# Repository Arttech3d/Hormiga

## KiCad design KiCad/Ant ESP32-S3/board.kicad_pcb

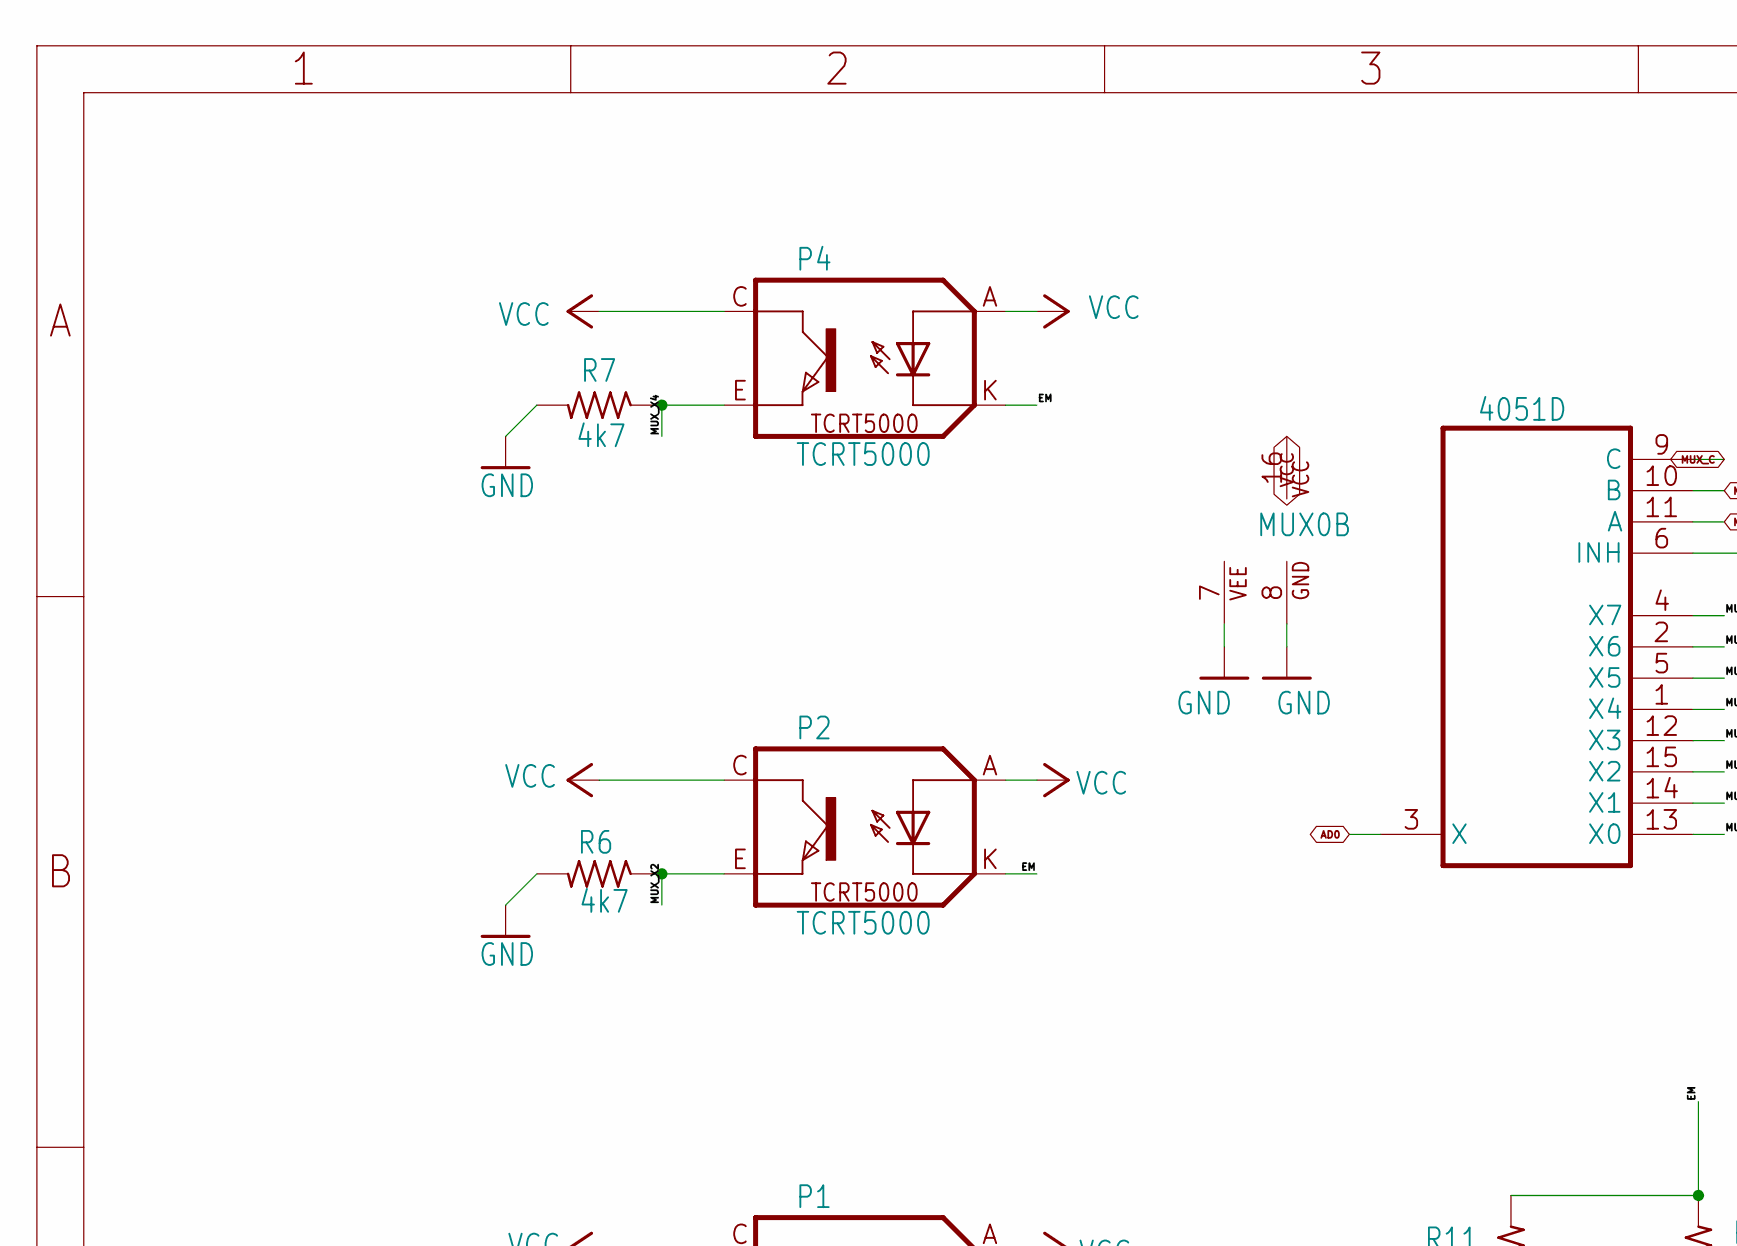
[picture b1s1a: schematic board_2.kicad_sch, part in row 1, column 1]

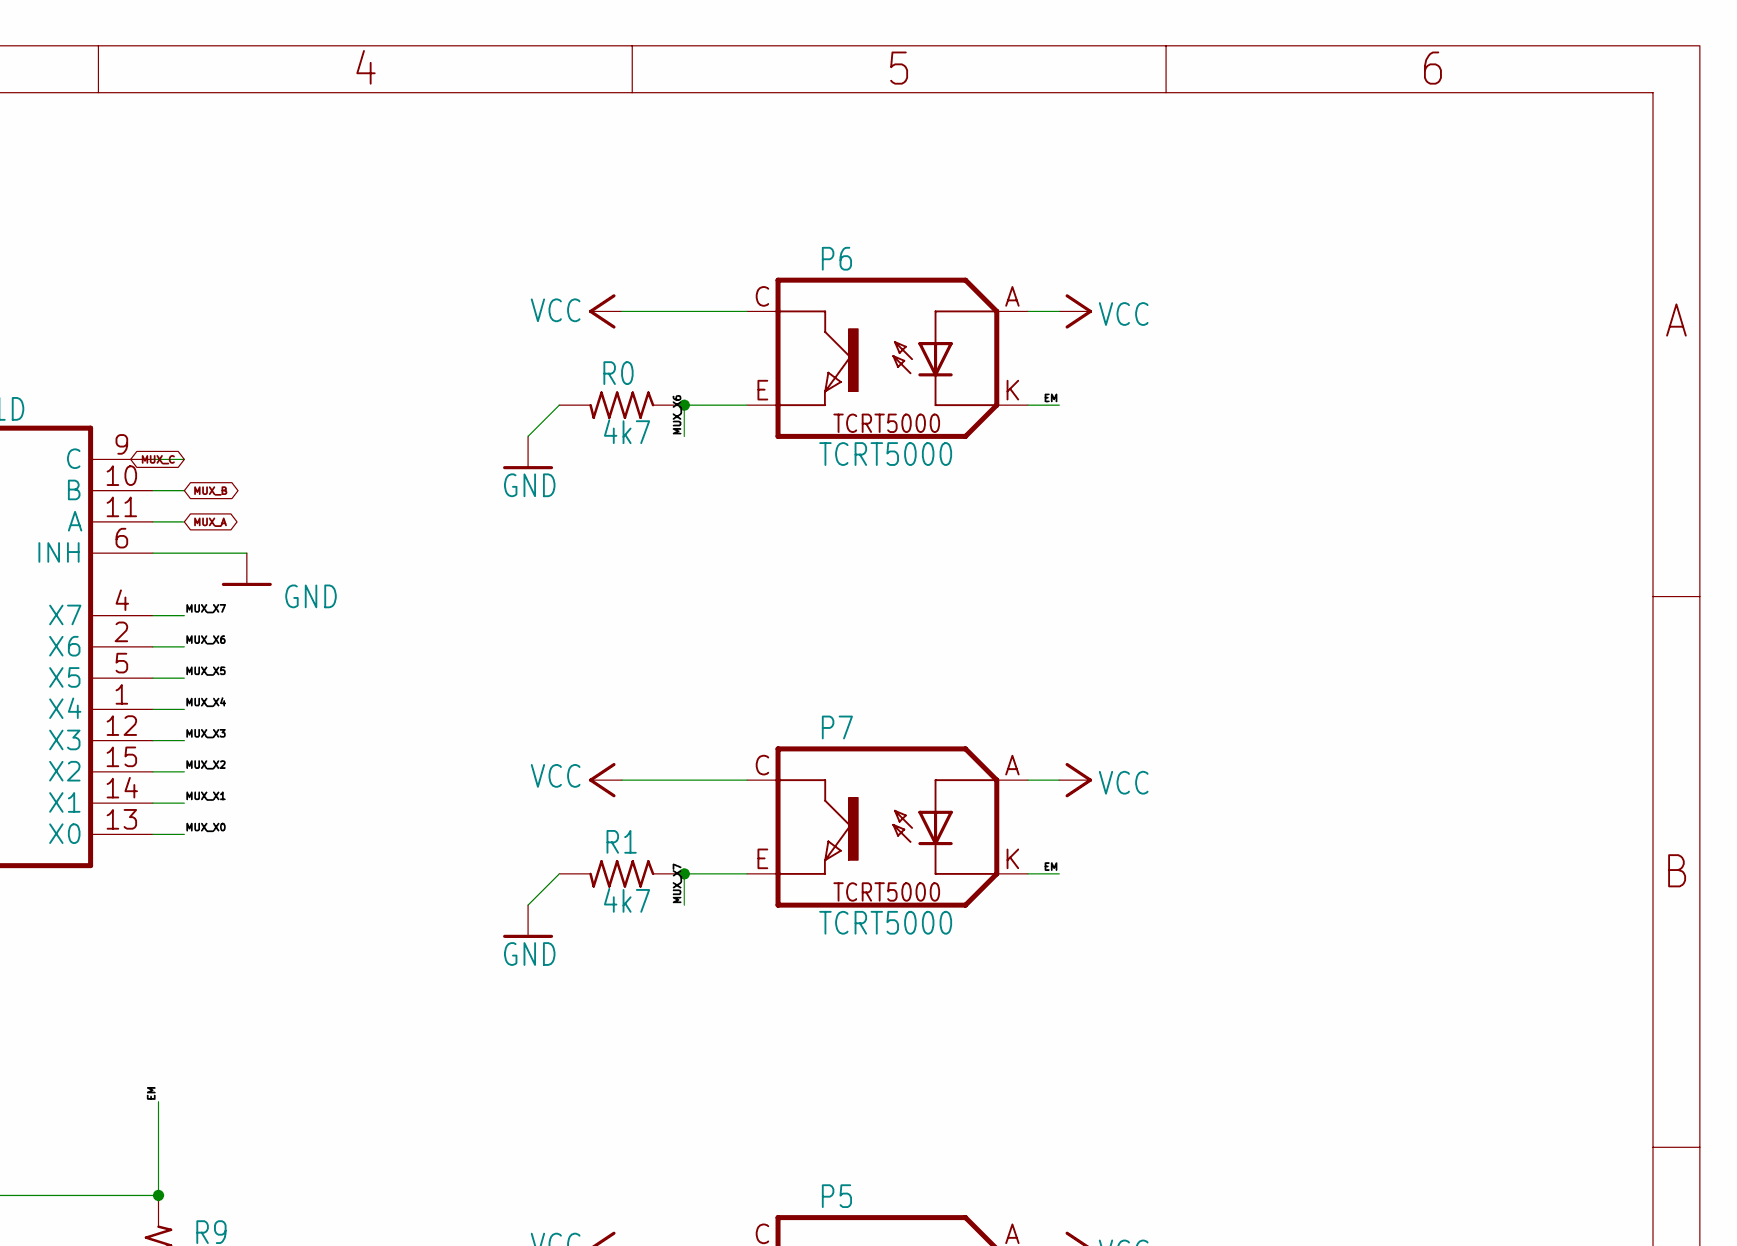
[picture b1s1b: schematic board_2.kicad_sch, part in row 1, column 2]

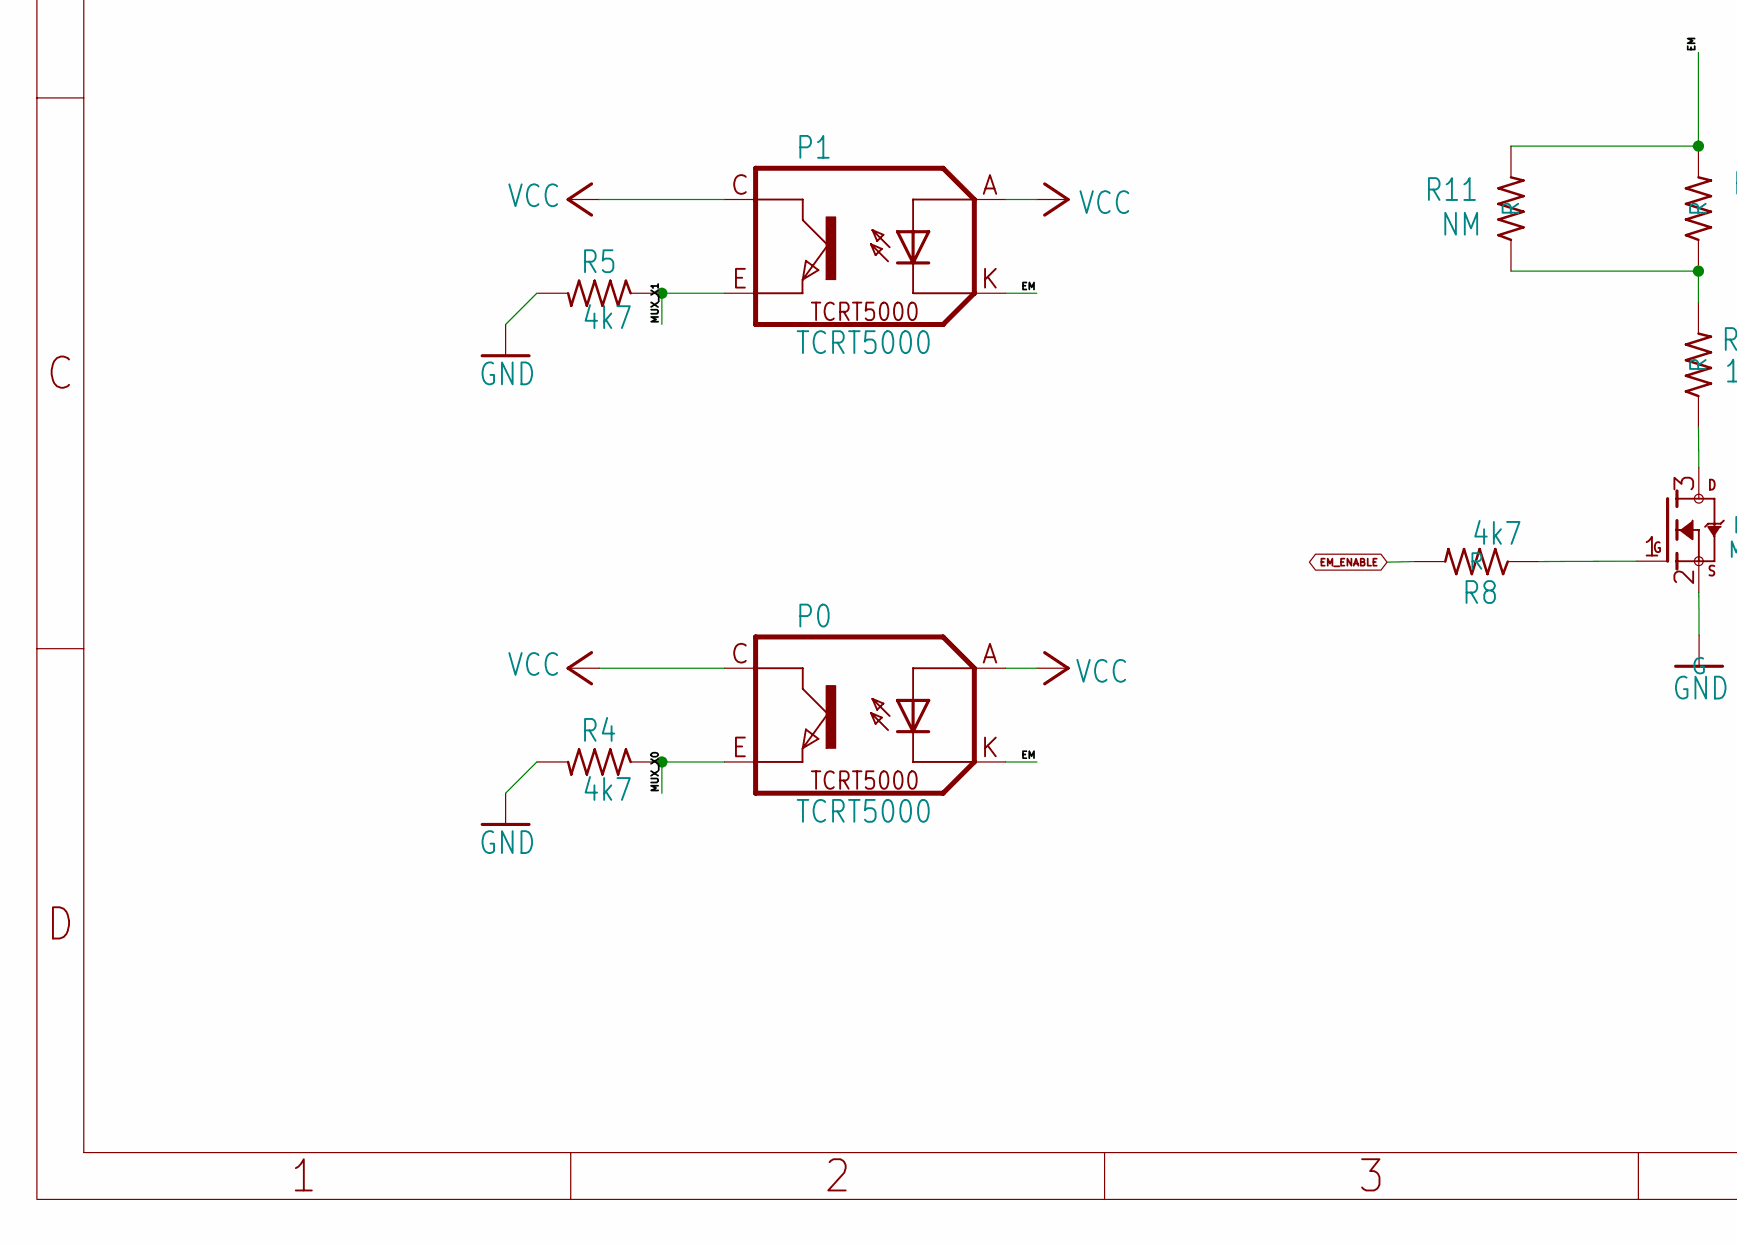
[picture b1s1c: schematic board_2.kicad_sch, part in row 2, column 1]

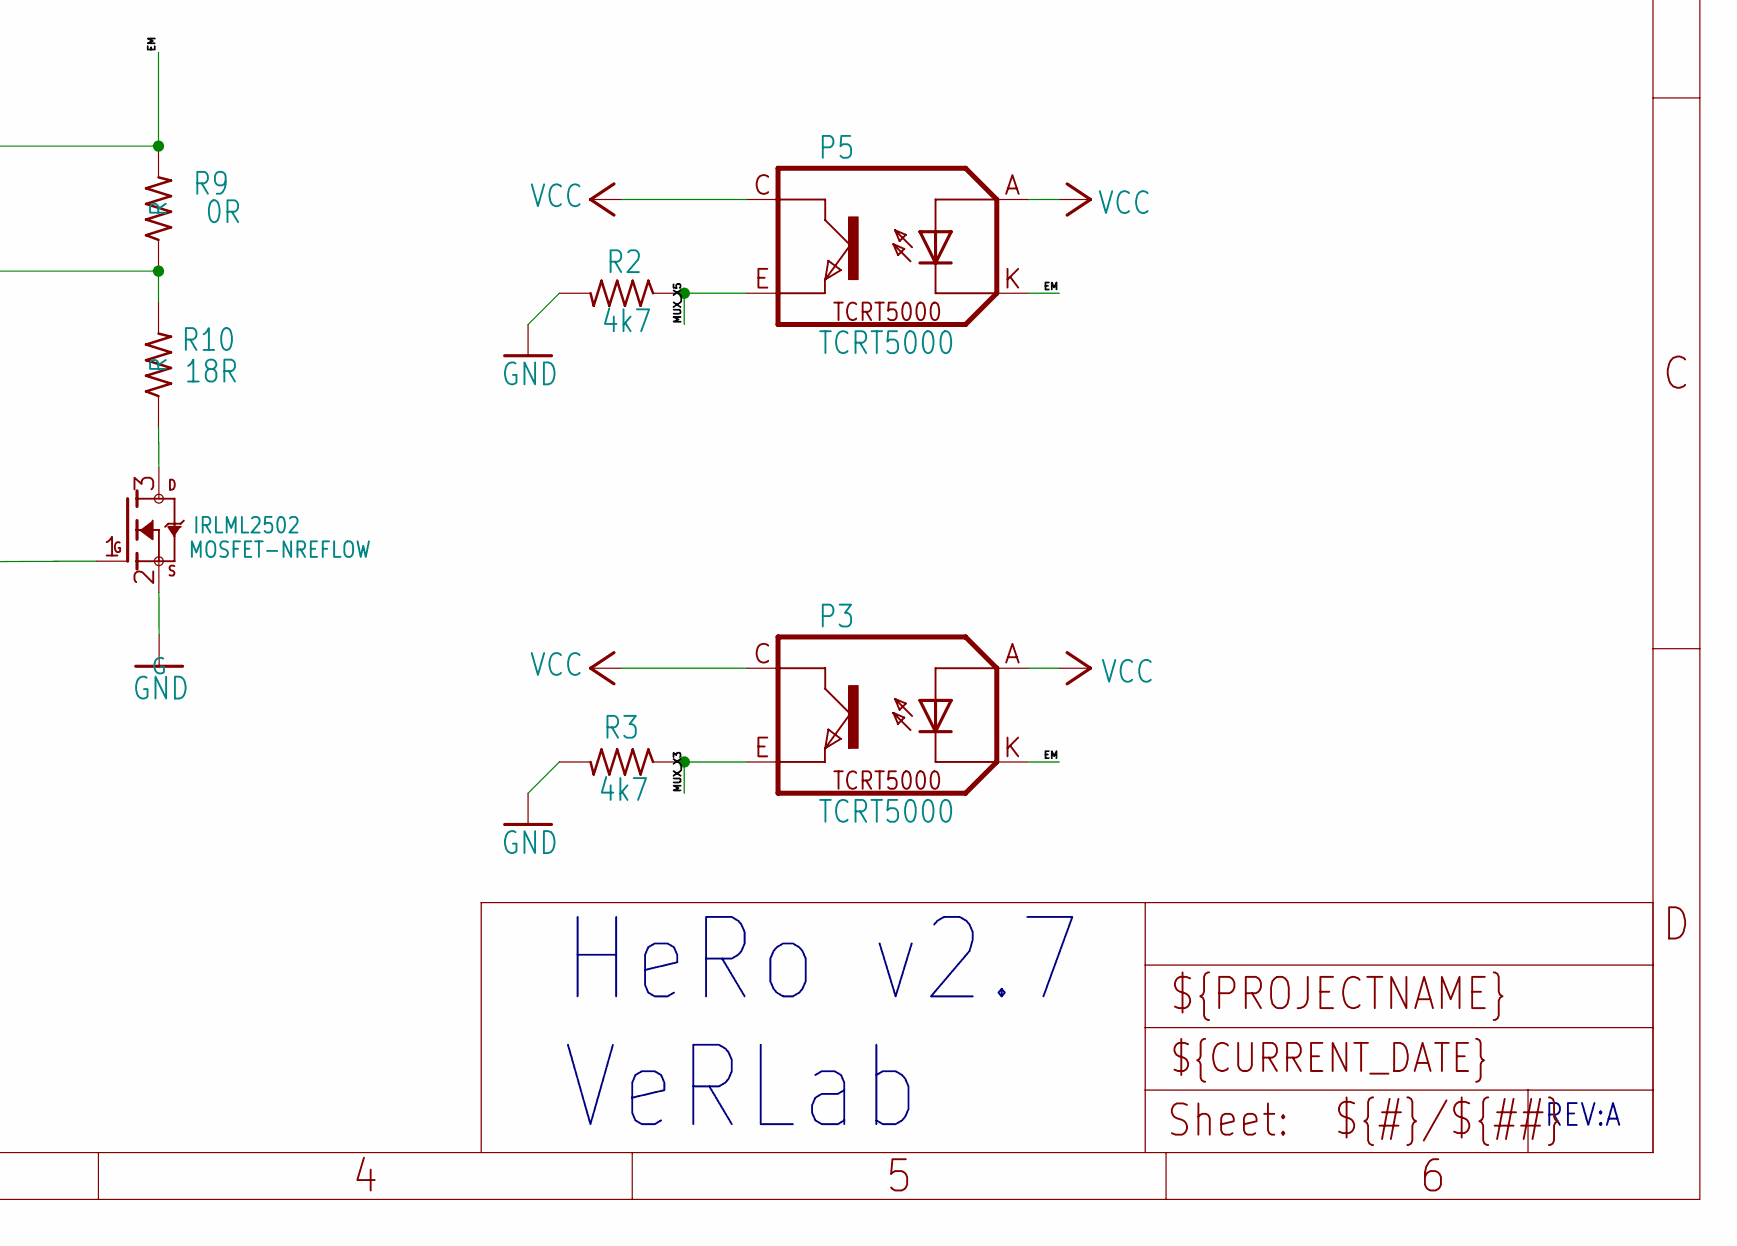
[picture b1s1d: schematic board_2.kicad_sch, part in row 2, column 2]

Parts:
IRLML2502: MOSFET-NREFLOW; SOT23
MUX0: 4051D; SO16
P0, P1, P2, P3, P4, P5, P6, P7: TCRT5000
R0, R1, R2, R3, R4, R5, R6, R7: 4k7; M0805
R8: 4k7; R0805
R9: 0R; R0805
R10: 18R; R0805
R11: NM; R0805

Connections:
/<p>Proximity Sensors</p>/EM: P0.K (CATHODE), P1.K (CATHODE), P2.K (CATHODE), P3.K (CATHODE), P4.K (CATHODE), P5.K (CATHODE), P6.K (CATHODE), P7.K (CATHODE), R9.2, R11.2
/<p>Proximity Sensors</p>/MUX_X0: MUX0.13 (X0), P0.E (EMITTER), R4.1
/<p>Proximity Sensors</p>/MUX_X1: MUX0.14 (X1), P1.E (EMITTER), R5.1
/<p>Proximity Sensors</p>/MUX_X2: MUX0.15 (X2), P2.E (EMITTER), R6.1
/<p>Proximity Sensors</p>/MUX_X3: MUX0.12 (X3), P3.E (EMITTER), R3.1
/<p>Proximity Sensors</p>/MUX_X4: MUX0.1 (X4), P4.E (EMITTER), R7.1
/<p>Proximity Sensors</p>/MUX_X5: MUX0.5 (X5), P5.E (EMITTER), R2.1
/<p>Proximity Sensors</p>/MUX_X6: MUX0.2 (X6), P6.E (EMITTER), R0.1
/<p>Proximity Sensors</p>/MUX_X7: MUX0.4 (X7), P7.E (EMITTER), R1.1
AD0: MUX0.3 (X); also elsewhere on the board
EM_ENABLE: R8.2; also elsewhere on the board
GND: IRLML2502.2 (S), MUX0.6 (INH), MUX0.7 (VEE), MUX0.8 (GND), R0.2, R1.2, R2.2, R3.2, R4.2, R5.2, R6.2, R7.2; also elsewhere on the board
MUX_A: MUX0.11 (A); also elsewhere on the board
MUX_B: MUX0.10 (B); also elsewhere on the board
MUX_C: MUX0.9 (C); also elsewhere on the board
unnamed: IRLML2502.3 (D), R10.1
unnamed: IRLML2502.1 (G), R8.1
unnamed: R9.1, R10.2, R11.1
VCC: MUX0.16 (VCC), P0.A (ANODE), P0.C (COLLECTOR), P1.A (ANODE), P1.C (COLLECTOR), P2.A (ANODE), P2.C (COLLECTOR), P3.A (ANODE), P3.C (COLLECTOR), P4.A (ANODE), P4.C (COLLECTOR), P5.A (ANODE), P5.C (COLLECTOR), P6.A (ANODE), P6.C (COLLECTOR), P7.A (ANODE), P7.C (COLLECTOR); also elsewhere on the board

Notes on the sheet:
HeRo v2.7 VeRLab
REV:A

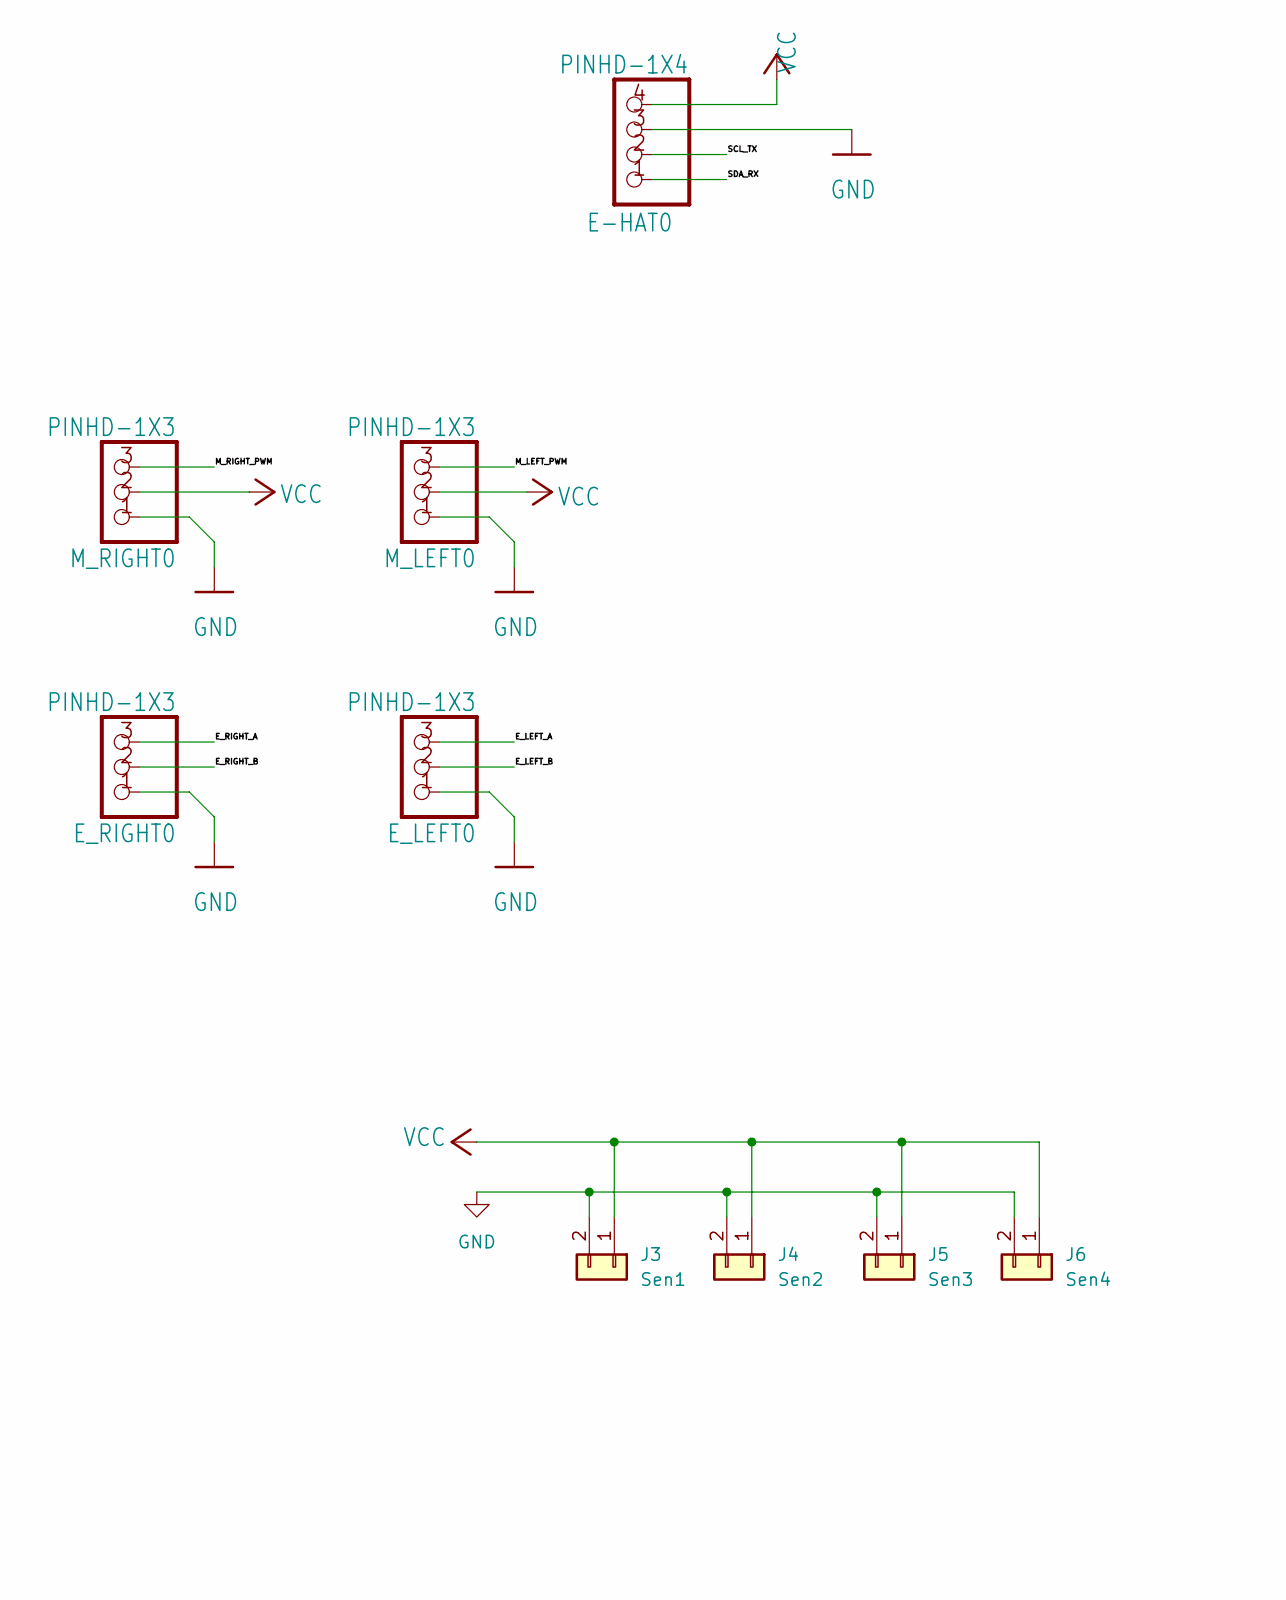
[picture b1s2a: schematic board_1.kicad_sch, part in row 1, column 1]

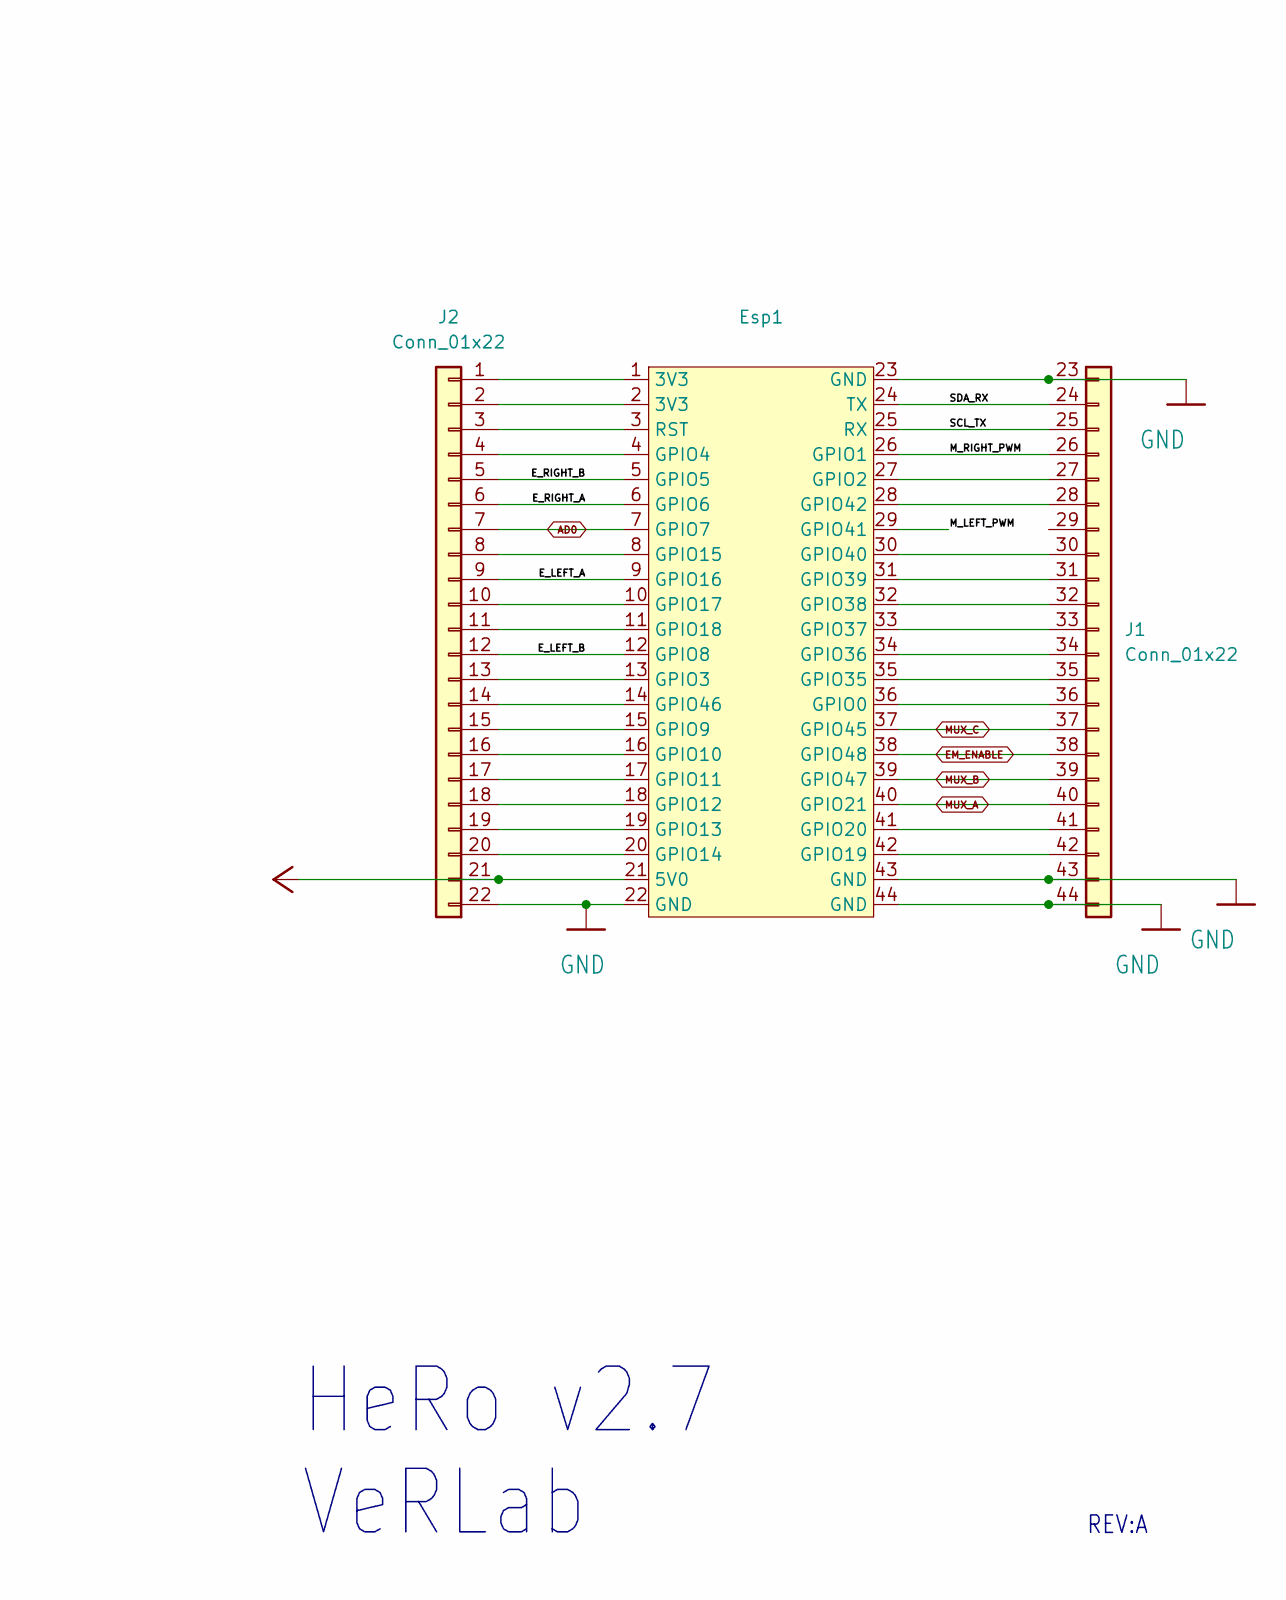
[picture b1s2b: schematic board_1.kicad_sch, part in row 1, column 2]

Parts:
E-HAT0: PINHD-1X4; 1X04
E_LEFT0: PINHD-1X3; 1X03
E_RIGHT0: PINHD-1X3; 1X03
Esp1: Untitled
J1, J2: Conn_01x22; PinHeader_1x22_P2.54mm_Vertical
J3: Sen1; PinHeader_1x02_P2.00mm_Vertical
J4: Sen2; PinHeader_1x02_P2.00mm_Vertical
J5: Sen3; PinHeader_1x02_P2.00mm_Vertical
J6: Sen4; PinHeader_1x02_P2.00mm_Vertical
M_LEFT0: PINHD-1X3; 1X03
M_RIGHT0: PINHD-1X3; 1X03

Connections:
/<p>MCU and Motors</p>/E_LEFT_A: E_LEFT0.3, Esp1.9 (GPIO16), J2.9 (Pin_14)
/<p>MCU and Motors</p>/E_LEFT_B: E_LEFT0.2, Esp1.12 (GPIO8), J2.12 (Pin_11)
/<p>MCU and Motors</p>/E_RIGHT_A: E_RIGHT0.3, Esp1.6 (GPIO6), J2.6 (Pin_17)
/<p>MCU and Motors</p>/E_RIGHT_B: E_RIGHT0.2, Esp1.5 (GPIO5), J2.5 (Pin_18)
/<p>MCU and Motors</p>/M_LEFT_PWM: Esp1.29 (GPIO41), M_LEFT0.3
/<p>MCU and Motors</p>/M_RIGHT_PWM: Esp1.26 (GPIO1), J1.26 (Pin_4), M_RIGHT0.3
/<p>MCU and Motors</p>/SCL_TX: E-HAT0.2, Esp1.25 (RX), J1.25 (Pin_3)
/<p>MCU and Motors</p>/SDA_RX: E-HAT0.1, Esp1.24 (TX), J1.24
AD0: Esp1.7 (GPIO7), J2.7 (Pin_16); also elsewhere on the board
EM_ENABLE: Esp1.38 (GPIO48), J1.38 (Pin_16); also elsewhere on the board
GND: E-HAT0.3, E_LEFT0.1, E_RIGHT0.1, Esp1.22 (GND), Esp1.23 (GND), Esp1.43 (GND), Esp1.44 (GND), J1.23, J1.43 (Pin_21), J1.44 (Pin_22), J2.22 (Pin_1), J3.2, J4.2, J5.2, J6.2, M_LEFT0.1, M_RIGHT0.1; also elsewhere on the board
MUX_A: Esp1.40 (GPIO21), J1.40 (Pin_18); also elsewhere on the board
MUX_B: Esp1.39 (GPIO47), J1.39 (Pin_17); also elsewhere on the board
MUX_C: Esp1.37 (GPIO45), J1.37 (Pin_15); also elsewhere on the board
unnamed: Esp1.1 (3V3), J2.1
unnamed: Esp1.36 (GPIO0), J1.36 (Pin_14)
unnamed: Esp1.27 (GPIO2), J1.27 (Pin_5)
unnamed: Esp1.13 (GPIO3), J2.13 (Pin_10)
unnamed: Esp1.4 (GPIO4), J2.4 (Pin_19)
unnamed: Esp1.15 (GPIO9), J2.15 (Pin_8)
unnamed: Esp1.16 (GPIO10), J2.16 (Pin_7)
unnamed: Esp1.17 (GPIO11), J2.17 (Pin_6)
unnamed: Esp1.18 (GPIO12), J2.18 (Pin_5)
unnamed: Esp1.19 (GPIO13), J2.19 (Pin_4)
unnamed: Esp1.20 (GPIO14), J2.20 (Pin_3)
unnamed: Esp1.8 (GPIO15), J2.8 (Pin_15)
unnamed: Esp1.10 (GPIO17), J2.10 (Pin_13)
unnamed: Esp1.11 (GPIO18), J2.11 (Pin_12)
unnamed: Esp1.42 (GPIO19), J1.42 (Pin_20)
unnamed: Esp1.41 (GPIO20), J1.41 (Pin_19)
unnamed: Esp1.35 (GPIO35), J1.35 (Pin_13)
unnamed: Esp1.34 (GPIO36), J1.34 (Pin_12)
unnamed: Esp1.33 (GPIO37), J1.33 (Pin_11)
unnamed: Esp1.32 (GPIO38), J1.32 (Pin_10)
unnamed: Esp1.31 (GPIO39), J1.31 (Pin_9)
unnamed: Esp1.30 (GPIO40), J1.30 (Pin_8)
unnamed: Esp1.28 (GPIO42), J1.28 (Pin_6)
unnamed: Esp1.14 (GPIO46), J2.14 (Pin_9)
unnamed: Esp1.3 (RST), J2.3 (Pin_20)
unnamed: Esp1.2 (3V3), J2.2 (Pin_21)
VCC: E-HAT0.4, Esp1.21 (5V0), J2.21 (Pin_2), J3.1, J4.1, J5.1, J6.1, M_LEFT0.2, M_RIGHT0.2; also elsewhere on the board

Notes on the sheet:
HeRo v2.7 VeRLab
REV:A

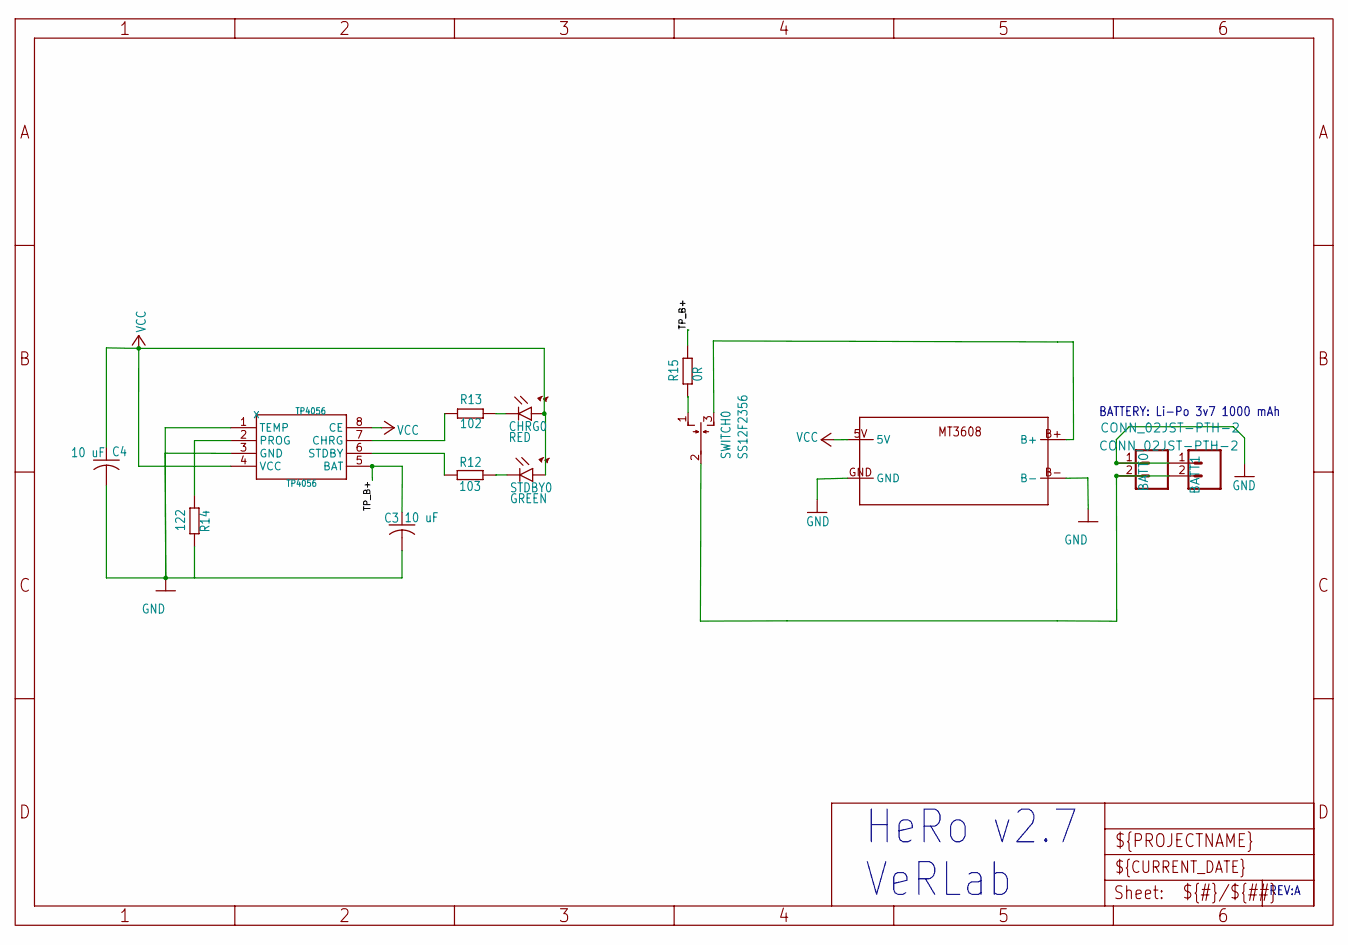
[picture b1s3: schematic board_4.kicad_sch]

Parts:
BATT0, BATT1: CONN_02JST-PTH-2; JST-2-PTH
C3, C4: 10 uF; C0603_420
CHRG0: RED; SML0805
MT3608: MT3608
R12: 103; R0805
R13: 102; R0805
R14: 122; R0603
R15: 0R; R0805
STDBY0: GREEN; SML0805
SWITCH0: SS12F2356; HH3T90
TP4056: TP4056; SOP

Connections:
/<p>Power Supply</p>/TP_B+: C3.1, R15.2, TP4056.5 (BAT)
GND: BATT0.1, BATT1.1, C3.2, C4.2, MT3608.B-, MT3608.GND, TP4056.1 (TEMP), TP4056.3 (GND); also elsewhere on the board
unnamed: CHRG0.C, R13.2
unnamed: R12.2, STDBY0.C
unnamed: R15.1, SWITCH0.1 (O)
unnamed: BATT0.2, BATT1.2, SWITCH0.2
unnamed: MT3608.B+, SWITCH0.3 (S)
unnamed: R13.1, TP4056.7 (CHRG)
unnamed: R14.2, TP4056.2 (PROG)
unnamed: R12.1, TP4056.6 (STDBY)
VCC: C4.1, CHRG0.A, MT3608.5V, STDBY0.A, TP4056.4 (VCC), TP4056.8 (CE); also elsewhere on the board

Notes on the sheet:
REV:A
HeRo v2.7 VeRLab
BATTERY: Li-Po 3v7 1000 mAh

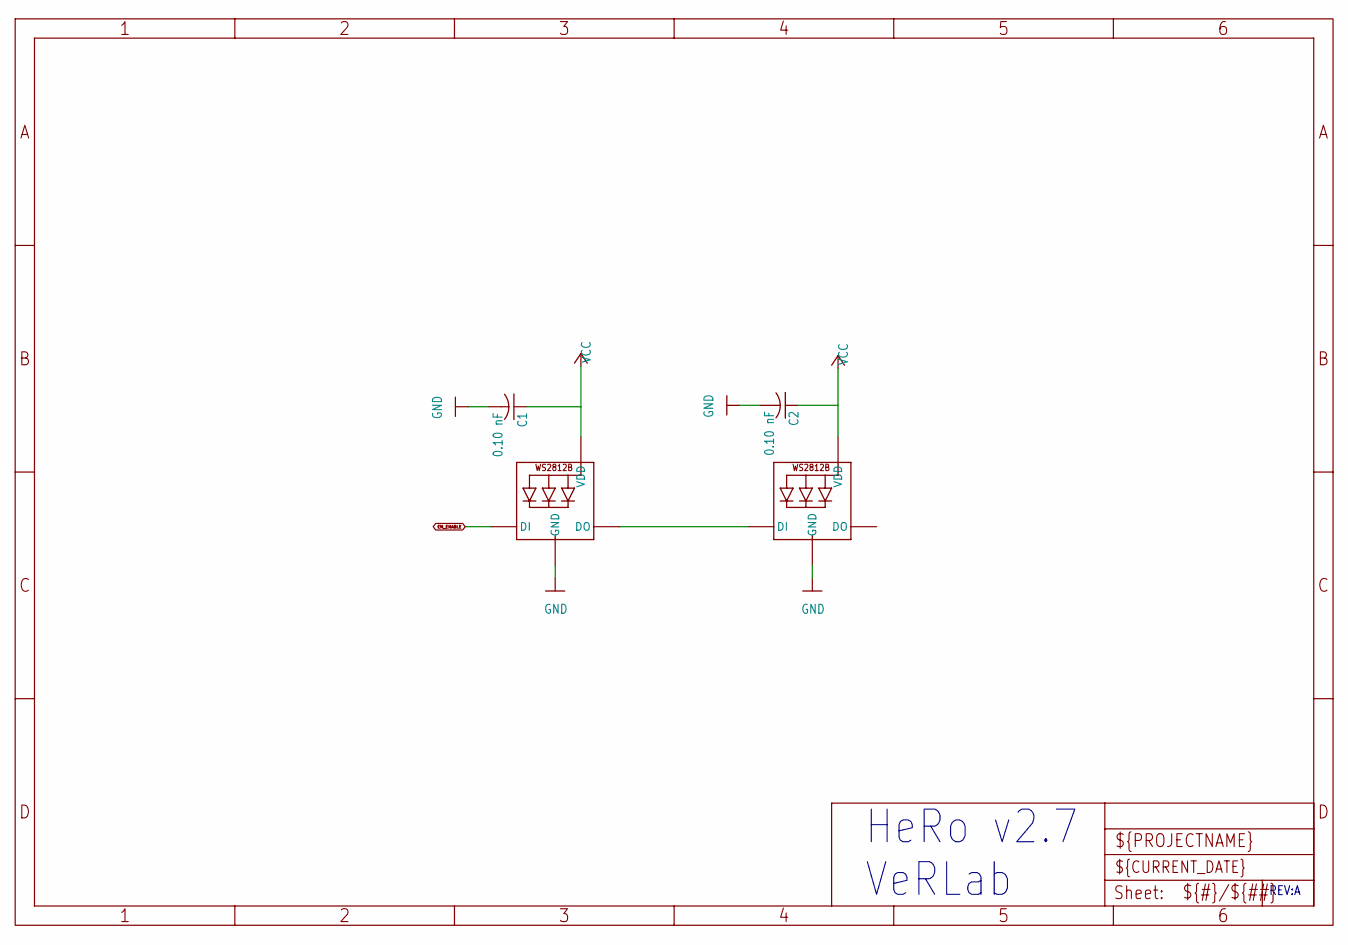
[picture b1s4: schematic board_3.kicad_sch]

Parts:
C1, C2: 0.10 nF; C0603_348
LED0, LED1: WS2812B5050; WS2812B

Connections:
EM_ENABLE: LED0.4-DIN (DI); also elsewhere on the board
GND: C1.2, C2.2, LED0.3-GND (GND), LED1.3-GND (GND); also elsewhere on the board
unnamed: LED0.2-DOUT (DO), LED1.4-DIN (DI)
VCC: C1.1, C2.1, LED0.1-VDD (VDD), LED1.1-VDD (VDD); also elsewhere on the board

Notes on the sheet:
HeRo v2.7 VeRLab
REV:A

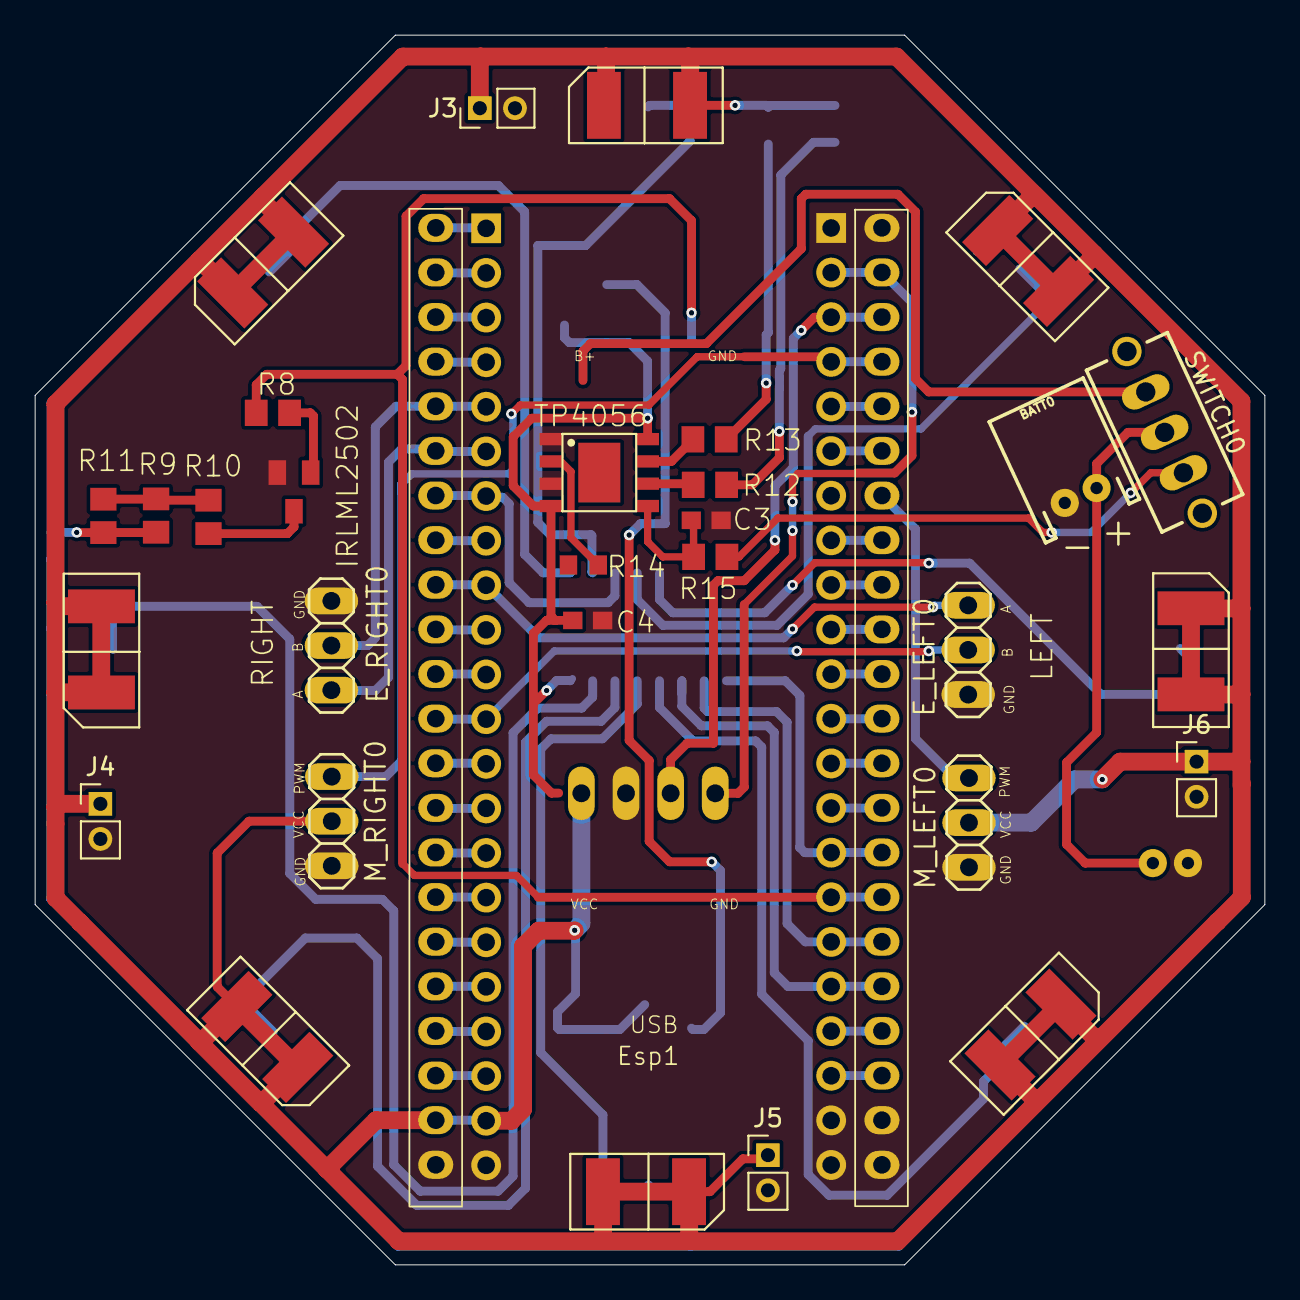
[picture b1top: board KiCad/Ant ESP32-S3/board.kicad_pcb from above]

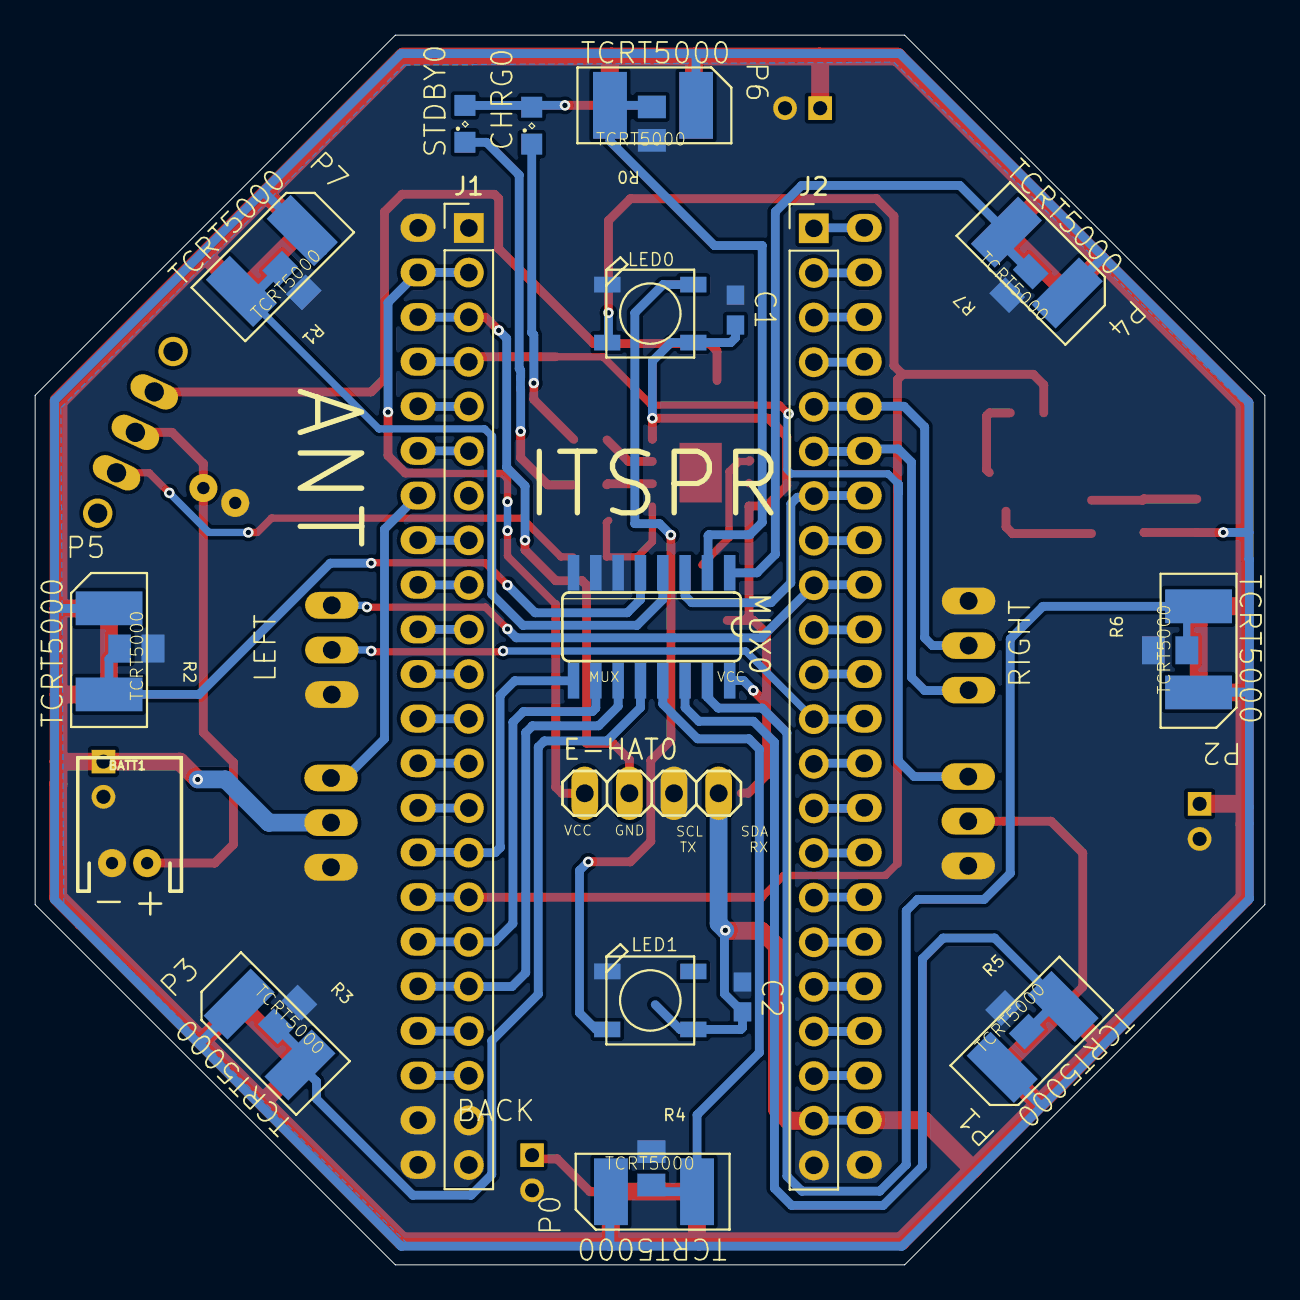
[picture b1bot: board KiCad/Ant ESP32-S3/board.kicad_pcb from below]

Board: 2 copper layers, 70.0 x 70.0 mm, 50 parts (27 on the bottom side), 62 nets.
